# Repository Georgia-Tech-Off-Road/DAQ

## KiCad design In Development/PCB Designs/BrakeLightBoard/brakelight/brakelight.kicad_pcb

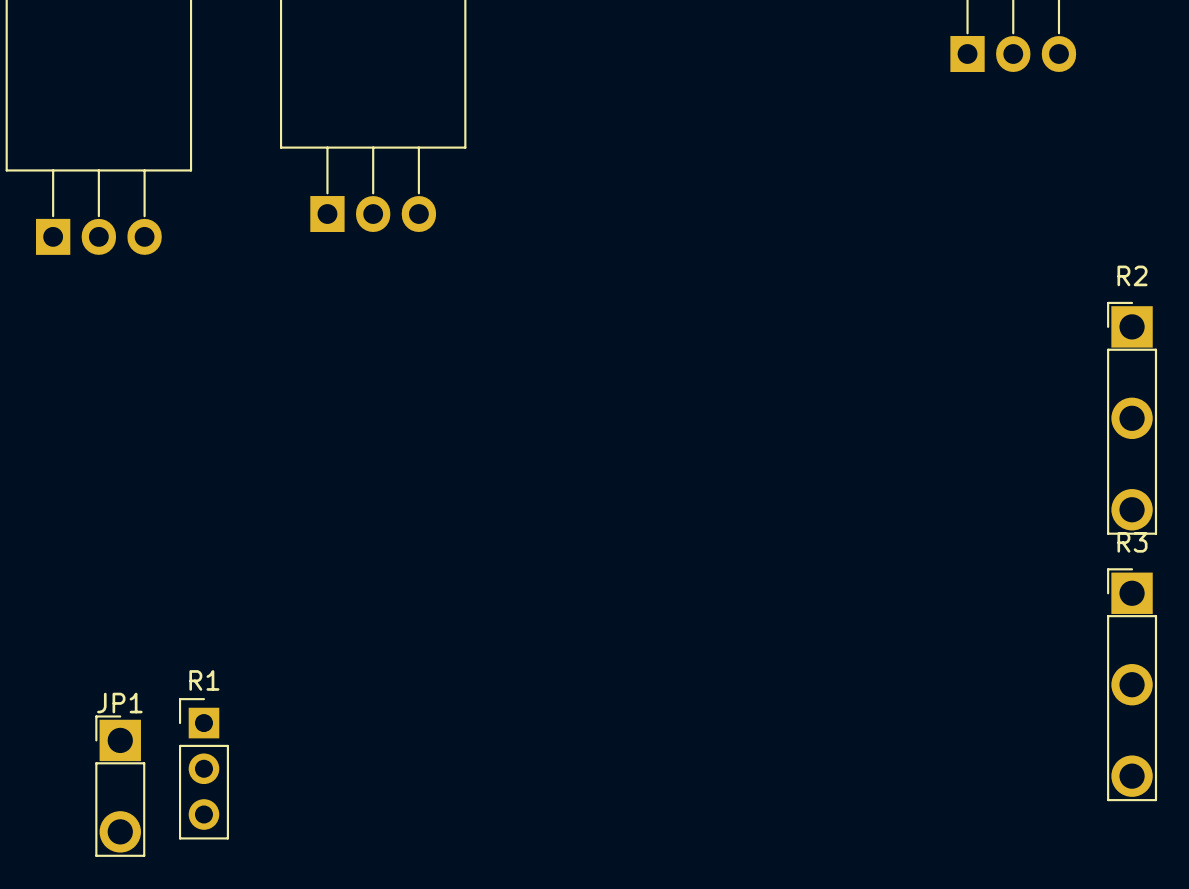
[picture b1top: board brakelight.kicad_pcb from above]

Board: 2 copper layers, 7 parts (0 on the bottom side), 3 nets, no tracks yet.

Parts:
IC3: 78XXL; TO-220-3_Horizontal_TabDown
JP1: PINHD-1X2; PinHeader_1x02_P5.08mm_Vertical
Q1, Q2: SUP75N06-08; TO-220-3_Horizontal_TabDown
R1: R-TRIMM74W; PinHeader_1x03_P2.54mm_Vertical
R2, R3: 100K; PinHeader_1x03_P5.08mm_Vertical

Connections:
GND: Q1.3, Q2.3, R1.3, R2.2, R3.2
unnamed: Q1.1, R2.1
unnamed: Q2.1, R3.1

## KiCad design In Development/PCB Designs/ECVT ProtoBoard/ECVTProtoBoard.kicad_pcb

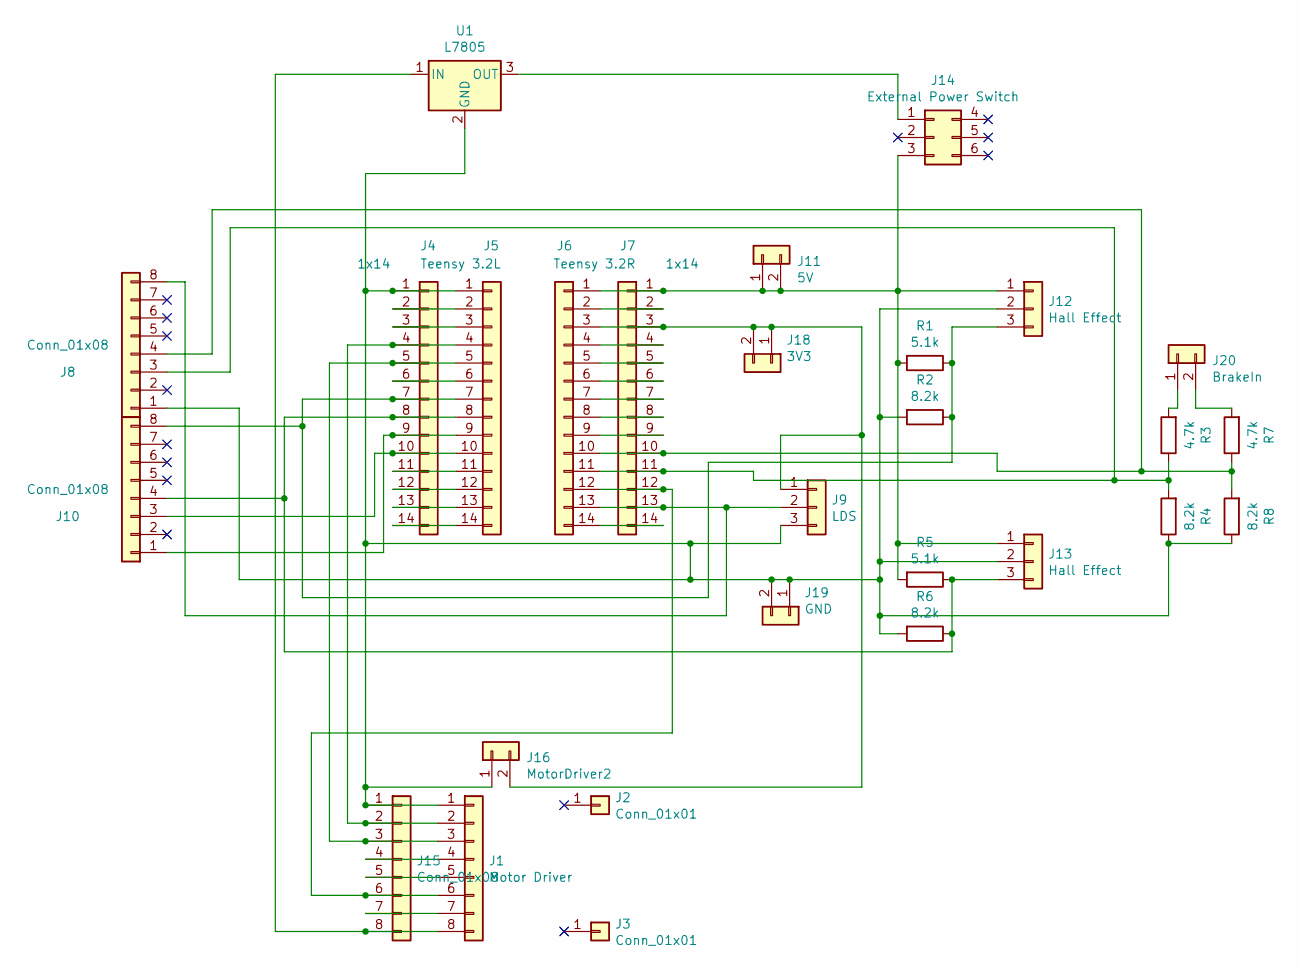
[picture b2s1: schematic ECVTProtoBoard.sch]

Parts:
J1: Motor Driver; PinHeader_1x08_P2.54mm_Vertical
J2, J3: Conn_01x01; PinHeader_1x01_P2.54mm_Vertical
J4, J7: 1x14; PinHeader_1x14_P2.54mm_Vertical
J5: Teensy 3.2L; PinHeader_1x14_P2.54mm_Vertical
J6: Teensy 3.2R; PinHeader_1x14_P2.54mm_Vertical
J8, J10: Conn_01x08; PinHeader_1x08_P2.00mm_Vertical
J9: LDS; PinHeader_1x03_P5.08mm_Vertical
J11: 5V; PinHeader_1x02_P2.54mm_Vertical
J12, J13: Hall Effect; PinHeader_1x03_P5.08mm_Vertical
J14: External Power Switch; PinHeader_2x03_P2.54mm_Vertical
J15: Conn_01x08; PinHeader_1x08_P2.54mm_Vertical
J16: MotorDriver2; PinHeader_1x02_P2.54mm_Vertical
J18: 3V3; PinHeader_1x02_P2.54mm_Vertical
J19: GND; PinHeader_1x02_P2.54mm_Vertical
J20: BrakeIn; PinHeader_1x02_P5.08mm_Vertical
R1, R5: 5.1k; R_Axial_DIN0207_L6.3mm_D2.5mm_P7.62mm_Horizontal
R2, R4, R6, R8: 8.2k; R_Axial_DIN0207_L6.3mm_D2.5mm_P7.62mm_Horizontal
R3, R7: 4.7k; R_Axial_DIN0207_L6.3mm_D2.5mm_P7.62mm_Horizontal
U1: L7805; TO-220-3_Horizontal_TabDown

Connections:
unnamed: J1.1, J4.1, J5.1, J8.1, J9.3, J12.2, J13.2, J15.1, J16.1, J19.1, J19.2, R2.2, R4.1, R6.2, R8.1, U1.2 (GND)
unnamed: J1.2, J4.4, J5.4, J15.2
unnamed: J1.3, J4.5, J5.5, J15.3
unnamed: J1.4, J15.4
unnamed: J1.5, J15.5
unnamed: J1.6, J6.12, J7.12, J15.6
unnamed: J1.7, J15.7
unnamed: J1.8, J15.8, U1.1 (IN)
unnamed: J4.2, J5.2
unnamed: J4.3, J5.3
unnamed: J4.6, J5.6
unnamed: J4.11, J5.11
unnamed: J4.12, J5.12
unnamed: J4.13, J5.13
unnamed: J4.14, J5.14
unnamed: J6.2, J7.2
unnamed: J6.4, J7.4
unnamed: J6.5, J7.5
unnamed: J6.6, J7.6
unnamed: J6.7, J7.7
unnamed: J6.8, J7.8
unnamed: J6.9, J7.9
unnamed: J6.10, J7.10, J8.4, R7.1, R8.2
unnamed: J6.11, J7.11, J8.3, R3.1, R4.2
unnamed: J6.13, J7.13, J8.8, J9.2
unnamed: J6.14, J7.14
unnamed: J4.9, J5.9, J10.1
unnamed: J4.10, J5.10, J10.3
unnamed: J4.8, J5.8, J10.4, J13.3, R5.1, R6.1
unnamed: J4.7, J5.7, J10.8, J12.3, R1.1, R2.1
unnamed: J6.1, J7.1, J11.1, J11.2, J12.1, J13.1, J14.3, R1.2, R5.2
unnamed: J14.1, U1.3 (OUT)
unnamed: J6.3, J7.3, J9.1, J16.2, J18.1, J18.2
unnamed: J20.1, R3.2
unnamed: J20.2, R7.2

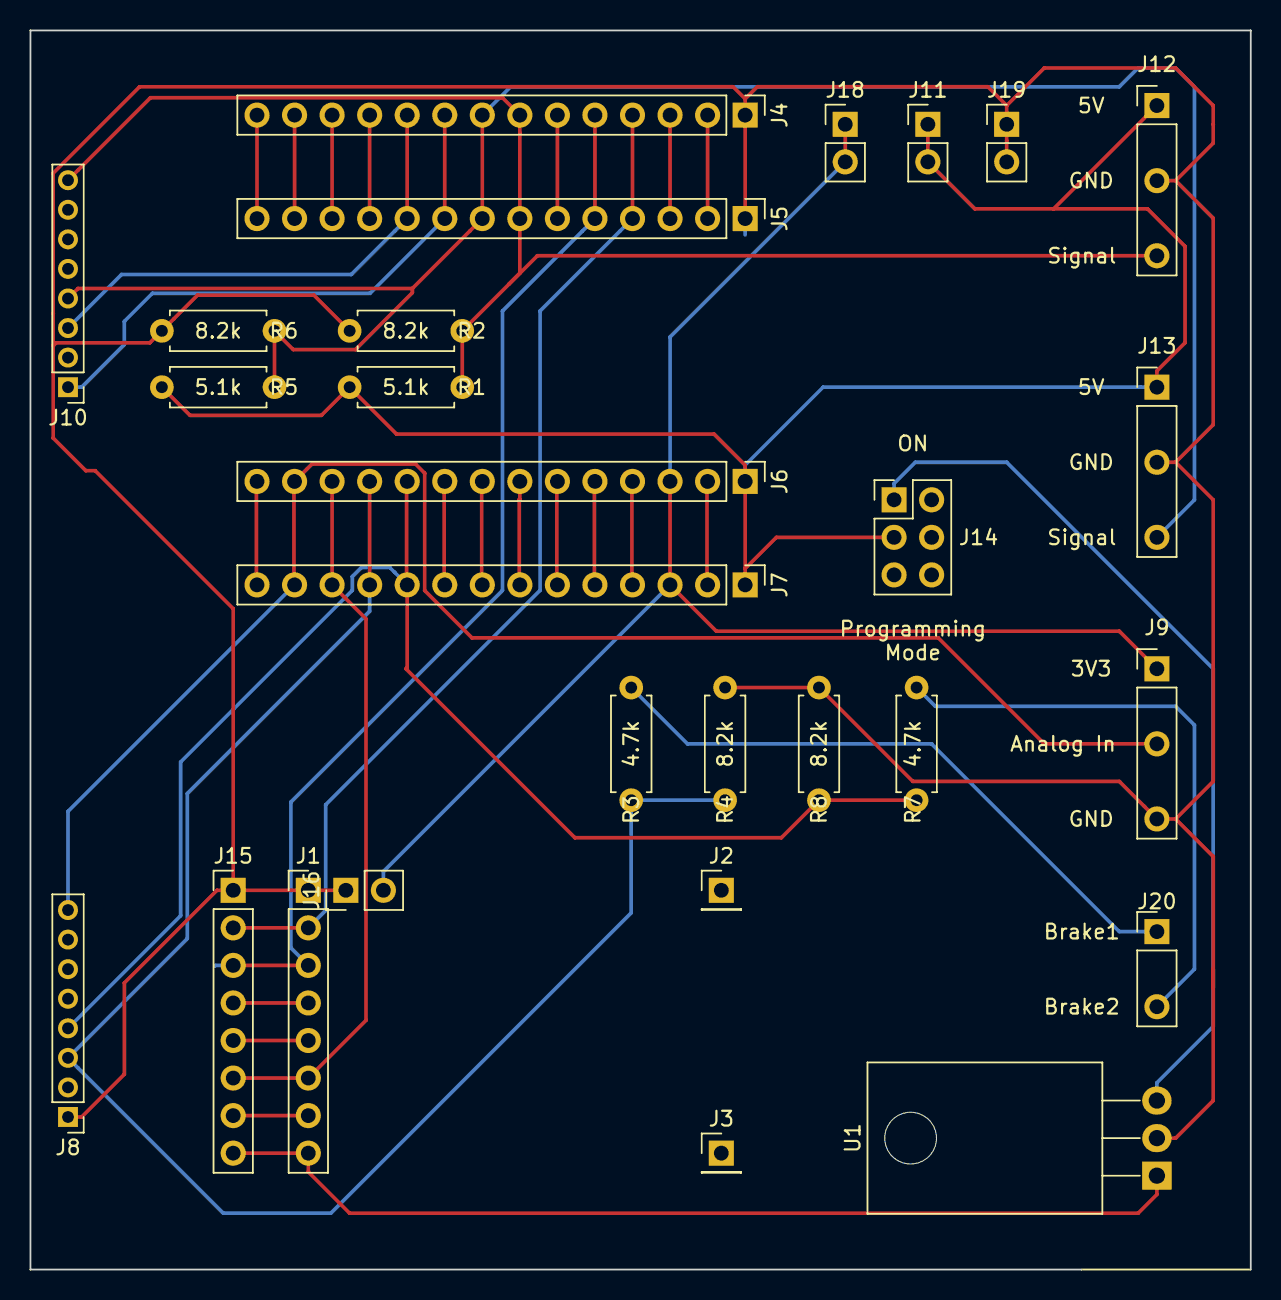
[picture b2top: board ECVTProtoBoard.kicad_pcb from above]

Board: 2 copper layers, 82.6 x 83.8 mm, 28 parts (0 on the bottom side), 35 nets.

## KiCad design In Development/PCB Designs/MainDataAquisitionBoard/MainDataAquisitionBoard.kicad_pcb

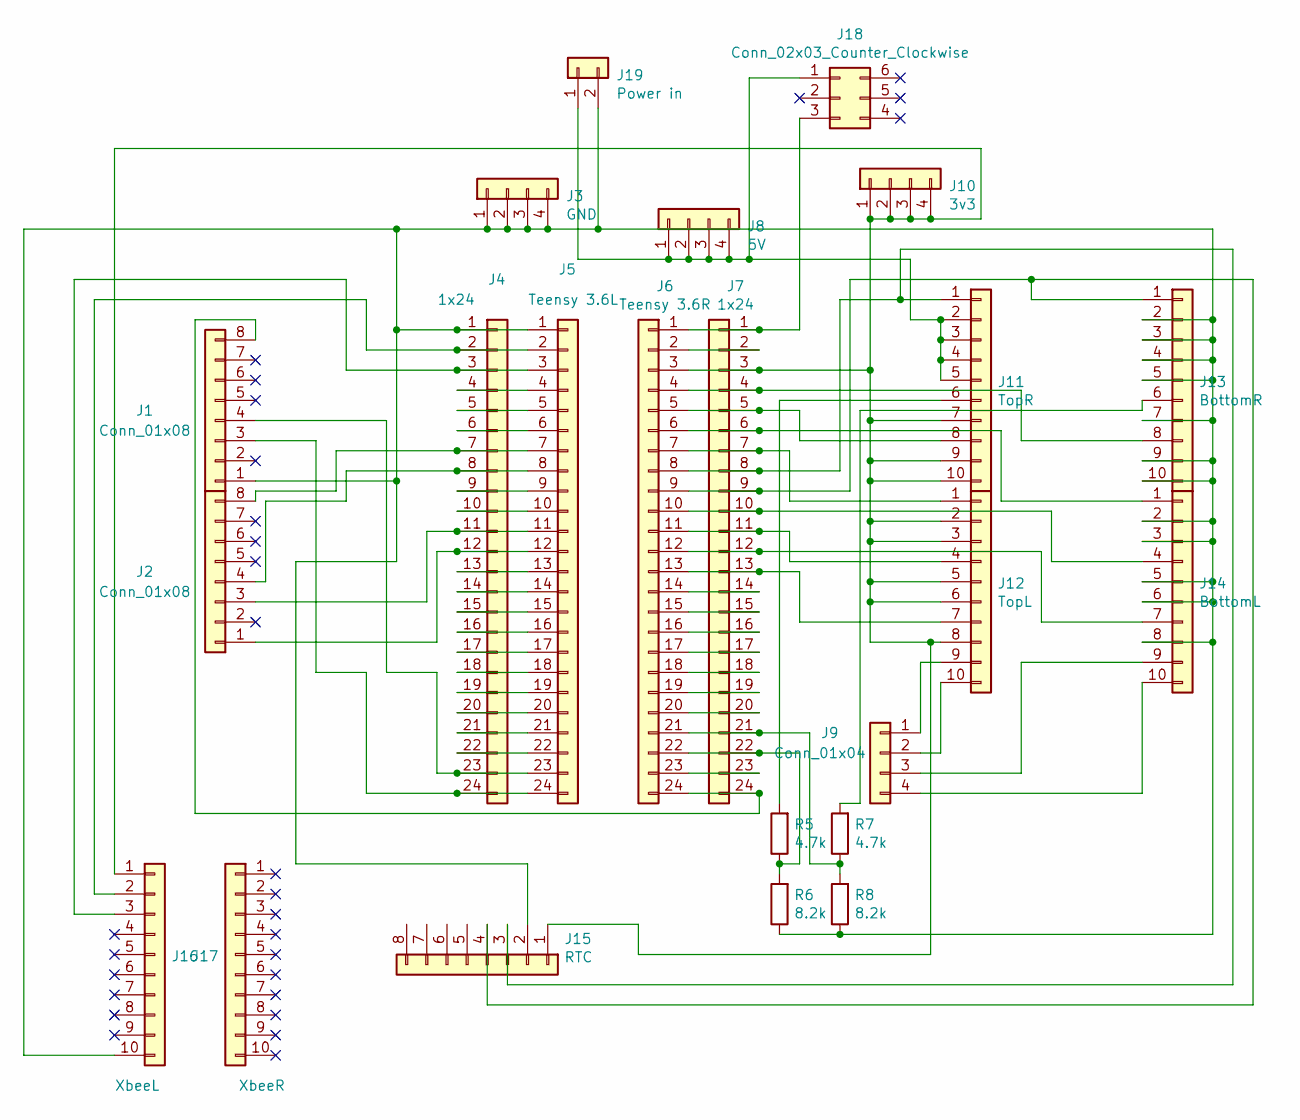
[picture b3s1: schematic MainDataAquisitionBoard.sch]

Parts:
J1, J2: Conn_01x08; PinHeader_1x08_P2.00mm_Vertical
J3: GND; PinHeader_1x04_P2.54mm_Vertical
J4, J7: 1x24; PinHeader_1x24_P2.54mm_Vertical
J5: Teensy 3.6L; PinHeader_1x24_P2.54mm_Vertical
J6: Teensy 3.6R; PinHeader_1x24_P2.54mm_Vertical
J8: 5V; PinHeader_1x04_P2.54mm_Vertical
J9: Conn_01x04; PinHeader_1x04_P2.54mm_Vertical
J10: 3v3; PinHeader_1x04_P2.54mm_Vertical
J11: TopR; PinHeader_1x10_P5.08mm_Vertical
J12: TopL; PinHeader_1x10_P5.08mm_Vertical
J13: BottomR; PinHeader_1x10_P5.08mm_Vertical
J14: BottomL; PinHeader_1x10_P5.08mm_Vertical
J15: RTC; PinHeader_1x08_P2.54mm_Vertical
J16: XbeeL; PinHeader_1x10_P2.54mm_Vertical
J17: XbeeR; PinHeader_1x10_P2.54mm_Vertical
J18: Conn_02x03_Counter_Clockwise; PinHeader_2x03_P2.54mm_Vertical
J19: Power in; PinHeader_1x02_P5.08mm_Vertical
R5, R7: 4.7k; R_Axial_DIN0207_L6.3mm_D2.5mm_P7.62mm_Horizontal
R6, R8: 8.2k; R_Axial_DIN0207_L6.3mm_D2.5mm_P7.62mm_Horizontal

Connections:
unnamed: J1.1, J3.1, J3.2, J3.3, J3.4, J4.1, J5.1, J13.2, J13.3, J13.4, J13.5, J13.7, J13.9, J13.10, J14.2, J14.3, J14.5, J14.6, J14.8, J15.2, J16.10, J19.2, R6.1, R8.1
unnamed: J1.3, J4.24, J5.24
unnamed: J1.4, J4.23, J5.23
unnamed: J1.8, J6.24, J7.24
unnamed: J2.1, J4.12, J5.12
unnamed: J2.3, J4.11, J5.11
unnamed: J2.4, J4.8, J5.8
unnamed: J2.8, J4.7, J5.7
unnamed: J4.4, J5.4
unnamed: J4.5, J5.5
unnamed: J4.6, J5.6
unnamed: J4.9, J5.9
unnamed: J4.10, J5.10
unnamed: J4.13, J5.13
unnamed: J4.14, J5.14
unnamed: J4.15, J5.15
unnamed: J4.16, J5.16
unnamed: J4.17, J5.17
unnamed: J4.18, J5.18
unnamed: J4.19, J5.19
unnamed: J4.20, J5.20
unnamed: J4.21, J5.21
unnamed: J4.22, J5.22
unnamed: J6.2, J7.2
unnamed: J6.14, J7.14
unnamed: J6.15, J7.15
unnamed: J6.16, J7.16
unnamed: J6.17, J7.17
unnamed: J6.18, J7.18
unnamed: J6.19, J7.19
unnamed: J6.20, J7.20
unnamed: J6.21, J7.21, R7.1, R8.2
unnamed: J6.22, J7.22, R5.1, R6.2
unnamed: J6.23, J7.23
unnamed: J6.3, J7.3, J10.1, J10.2, J10.3, J10.4, J11.7, J11.9, J11.10, J12.2, J12.3, J12.5, J12.6, J12.8, J15.1, J16.1
unnamed: J6.8, J7.8, J11.1, J15.3
unnamed: J8.1, J8.2, J8.3, J8.4, J11.2, J11.3, J11.4, J11.5, J18.1, J19.1
unnamed: J11.6, R5.2
unnamed: J6.5, J7.5, J11.8
unnamed: J6.7, J7.7, J12.1
unnamed: J6.11, J7.11, J12.4
unnamed: J6.13, J7.13, J12.7
unnamed: J9.1, J12.9
unnamed: J9.2, J12.10
unnamed: J6.9, J7.9, J13.1, J15.4
unnamed: J13.6, R7.2
unnamed: J6.4, J7.4, J13.8
unnamed: J6.6, J7.6, J14.1
unnamed: J6.10, J7.10, J14.4
unnamed: J6.12, J7.12, J14.7
unnamed: J9.3, J14.9
unnamed: J9.4, J14.10
unnamed: J4.2, J5.2, J16.2
unnamed: J4.3, J5.3, J16.3
unnamed: J6.1, J7.1, J18.3

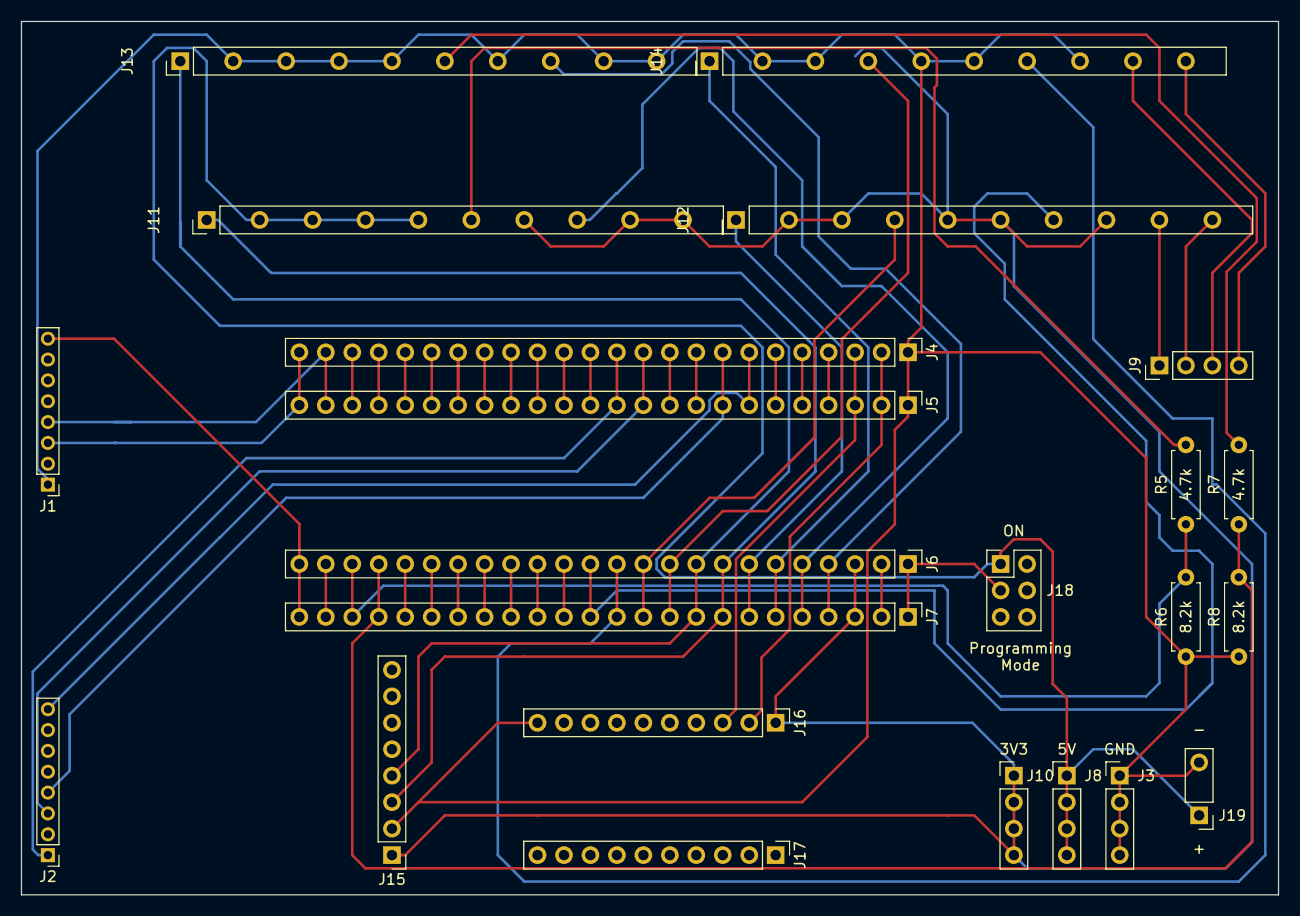
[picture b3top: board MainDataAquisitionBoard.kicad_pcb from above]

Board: 2 copper layers, 120.7 x 83.8 mm, 23 parts (0 on the bottom side), 55 nets.

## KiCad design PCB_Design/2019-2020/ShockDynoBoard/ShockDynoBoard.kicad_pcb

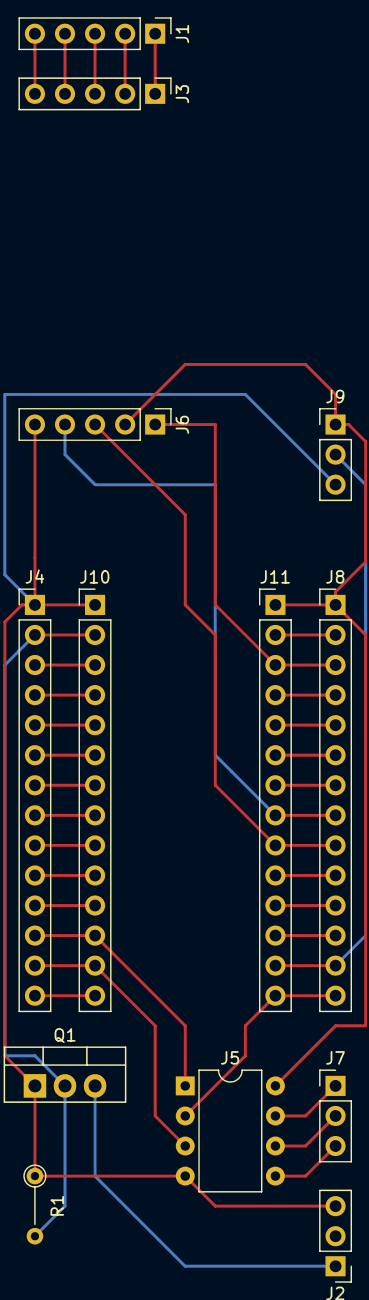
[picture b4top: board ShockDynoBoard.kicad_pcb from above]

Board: 2 copper layers, 13 parts (0 on the bottom side), 37 nets.

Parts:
J1: Load Cell; PinHeader_1x05_P2.54mm_Vertical
J2: ESC Switch; PinHeader_1x03_P2.54mm_Vertical
J3: HX711 L; PinHeader_1x05_P2.54mm_Vertical
J4, J8: 1x14; PinHeader_1x14_P2.54mm_Vertical
J5: MSP4131; DIP-8_W7.62mm
J6: HX711 R; PinHeader_1x05_P2.54mm_Vertical
J7: ESC; PinHeader_1x03_P2.54mm_Vertical
J9: LDS; PinHeader_1x03_P2.54mm_Vertical
J10: Teensy 3.2 L; PinHeader_1x14_P2.54mm_Vertical
J11: Teensy 3.2 R; PinHeader_1x14_P2.54mm_Vertical
Q1: MOSFET; TO-220-3_Vertical
R1: 20k; R_Axial_DIN0204_L3.6mm_D1.6mm_P5.08mm_Vertical

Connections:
unnamed: J1.1, J3.1
unnamed: J1.2, J3.2
unnamed: J1.3, J3.3
unnamed: J1.4, J3.4
unnamed: J1.5, J3.5
unnamed: J2.1, Q1.3
unnamed: J5.5, J7.3
unnamed: J5.6, J7.2
unnamed: J5.7, J7.1
unnamed: J2.3, J4.1, J5.4, J6.5, J9.3, J10.1, Q1.1, R1.1
unnamed: J4.2, J10.2, Q1.2, R1.2
unnamed: J4.3, J10.3
unnamed: J4.4, J10.4
unnamed: J4.5, J10.5
unnamed: J4.6, J10.6
unnamed: J4.7, J10.7
unnamed: J4.8, J10.8
unnamed: J4.9, J10.9
unnamed: J4.10, J10.10
unnamed: J4.11, J10.11
unnamed: J4.12, J5.1, J10.12
unnamed: J4.13, J5.3, J10.13
unnamed: J4.14, J10.14
unnamed: J5.8, J6.2, J8.1, J9.1, J11.1
unnamed: J8.2, J11.2
unnamed: J6.1, J8.3, J11.3
unnamed: J8.4, J11.4
unnamed: J8.5, J11.5
unnamed: J8.6, J11.6
unnamed: J8.7, J11.7
unnamed: J6.4, J8.8, J11.8
unnamed: J6.3, J8.9, J11.9
unnamed: J8.10, J11.10
unnamed: J8.11, J11.11
unnamed: J8.12, J11.12
unnamed: J8.13, J9.2, J11.13
unnamed: J5.2, J8.14, J11.14

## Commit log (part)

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2020-12-27 Testing if I can push to remote
2020-12-31 IMU330DHCX Final Code
2020-12-31 IMU330DHCX Header Upload
2021-01-03 Added the HE sensor case for Rev2
2021-01-14 Add ISM330DHCX Library
2021-01-15 Conceptual Brainstorming Changes
2021-01-15 Added diff library for eagle
2021-01-15 Added relevant mailing lists for recruitment emails.
2021-01-15 Updated .gitignore and cleaned up Eagle autosaves
2021-01-15 Removed Eagle Libraries
2021-01-16 Created HESensorRev3 case and added documentation
2021-01-16 Added STL Files for Printing
2021-01-16 Created file for IMU
2021-01-16 Increase ranges for accel, gyro, and data rates
2021-01-16 Documentation changes
2021-01-17 Eagle files for PCB
2021-01-18 Added schematic and board files
2021-01-20 Updated Eagle board and software
    Added female headers, routed HE inputs
    Added theoretical diff controller code basis
2021-01-23 Made minor edits to documentation
2021-01-23 Added step in eagle libraries guide
2021-01-27 Test example
2021-01-31 Added small functions to utility
2021-01-31 Changed Lib .readme
2021-01-31 Added automatic Arduino library symlinks generator
2021-02-01 Resized speed sensor case for larger shaft
2021-02-03 Fixed parts so that they can actually be assembled.
2021-02-05 Added STL Files for IMU Case Printing
2021-02-09 Renamed folder from "new_project" to "Dyno Board"
2021-02-10 Renamed folder and added Load Cell Manual.
2021-02-13 Fixed data being deleted after stopped collecting bug
2021-02-13 Added changes that I do not remember
2021-02-18 Created documentation for the engine dyno
2021-02-19 Added documentation for engine dyno
2021-02-19 Added lots of changes for first working prototype
2021-02-24 replaced old motor driver; added local libraries
2021-02-24 Minor bug fixes
2021-02-28 pcb from 02-28
2021-03-04 edited h-bridge
2021-03-04 Minor changes on PCB, ready for manufacturing
2021-03-07 Began work on UARTComms class and Sensor class
2021-03-07 small changes to Sensor
2021-03-07 added changes to update function
2021-03-07 Adding __init__ for EngineDyno Layout
2021-03-10 Pseudocoded rest of Comms functions to be written
2021-03-12 Reconstructed FreqMeasureMulti without using FreqMeasureMulti library
2021-03-12 Moved IMU Lib folder code to Libraries folder
2021-03-12 Moved Dyno code in Lib folder to Libraries folder
2021-03-16 Added functionality for zero rpm
2021-03-17 Finished Aux Daq Case
2021-03-19 Seven Segment Code done
2021-03-20 added matlab file for theoretical speed sensor calculations
2021-03-21 Added update for serial input
2021-03-21 Auto stash before merge of "differential_controller" and "origin/differential_controller"
2021-03-21 Fixed compilation errors and implemented switch/serial control mode
2021-03-24 Finished theoretical implementation using FreqMeasureMulti
2021-03-25 Adding data parser for recording and graphing data collected from sensors
2021-03-26 Adding the data parser to change bin data files in to usable data to graph and add to an excel sheet
2021-03-26 Reversed motor pins to work with new differential
2021-03-26 Working UARTComms and SDWrite libraries. Next step is extending Sensor functionality.
2021-03-26 temporary commit
2021-03-26 Tidying the parser and preparing for plotting
2021-03-26 Sensor updates, LDS example
2021-03-27 Fixed some problems with LDS example, Sensor id bug still exists---id needs to be 1 byte for now
2021-03-27 aux daq unit code with two sensors
2021-03-27 Quick fix for diff controller breaking when moving to state 1 and state2
2021-03-27 Added more sensor libraries
2021-03-27 Give to Akash code
2021-03-28 Changes from grind day
2021-03-30 Beginning data parser optimizations
2021-04-01 Need to change branches
2021-04-01 Small changes to DataCollection
2021-04-02 Adding more cleanup to parser
2021-04-02 Added functions to implement for data import
2021-04-02 Added Sensor ID's to Daata
2021-04-04 Before merge with aux_daq_util
2021-04-04 Adding most Import functionality and updating Data and SensorId accordingly
2021-04-04 Added Pinout image and modified Dyno_test to follow pinout
2021-04-06 Renamed Folder to Engine_Dyno
2021-04-06 Updated HEtest.ino to work with new HE Sensor library
2021-04-06 Added psedu-code/code for speed sensor?
    Please double-check
2021-04-07 Finished minimum worked version of SpeedSensor
2021-04-07 Added SpeedSensor to Sensor.h
2021-04-07 Cleaning up parser, adding csv file for data, and beginning update to Sensor objects and ID's
2021-04-07 Updating Sensor ID numbers
2021-04-07 hotfix
2021-04-07 Code ready for dyno test
2021-04-09 Added SerialTest.ino
2021-04-09 Git witchcraft merge
2021-04-10 Comments added
2021-04-11 Code uploaded for the 4/11/2021 test day
    Syntax errors fixed
2021-04-13 Code uploaded for test day 4/11/21
2021-04-17 Fixed errors with Sensor Class
2021-04-17 Adding data parsers
2021-04-17 Updated SensorId
2021-04-17 Changes to mock wireless testing
2021-04-17 Manual merge of dashboard into master
2021-04-21 Adding syntax fixes in import
2021-04-21 Changing serial port to None to get it working
2021-04-23 On the verge of glory
2021-04-25 pls no conflict
2021-04-28 Made better averaging algorithm for speed sensor
2021-05-01 Updated Dashboard Code (non-working)
2021-05-01 Display diff position on dashboard
2021-05-01 Added StateSensor and diff_state functionality for writing diff_state to h_seg on dash
2021-05-12 Updated documentation template
2021-06-02 DashHub code changes from Arizona
2021-06-18 Removed Documentation
2021-06-18 Removed Resources Folder
2021-06-26 Removed HallEffectSpeedSensor
2021-06-29 Removed Libraries
2021-07-08 Updates to First Dyno test
2021-08-21 Added ability to zero load cell
2021-09-03 Created new branch and folder for new 2022 aux_daq
2021-09-06 Added rough draft of shockdyno arduino code
2021-09-12 Added optional headers for strain gauge breakout
2021-09-12 added project for shock dyno
2021-09-19 Working on board files
2021-09-19 Minor DRC fixes and trace thickening
2021-09-19 Minor silkscreen changes
2021-09-19 completed shock dyno PCB schematic
2021-09-20 Boards designs before 9/19 design review
2021-09-22 Moved phat connector
2021-09-24 shock dyno PCB updates
2021-09-26 Just a bit of work I did on Tuesday
2021-09-26 Added kill motor scenario and fixed scale for motor_control
2021-09-26 added name to shock dyno PCB
2021-09-27 More work done to dash hub and dial, gps board added
2021-09-27 Adding design draft of comms testing board
2021-09-28 Finished everything except silkscreen
2021-09-29 final touches to shock dyno PCB
2021-09-29 Adding finished comms testing board
2021-09-29 Updated silkscreen
2021-09-29 final touches to shock dyno PCB part 3
2021-10-01 Linear Regulator
2021-10-06 Added wireless receiver PCB
2021-10-08 Added new linear regulator and XBee silkscreen to dashhub
2021-10-10 Added gps to dashhub
2021-10-15 Added OLED
2021-10-17 Added missing capacitor values
2021-10-17 Moving stuff around on the dashhub #pain
2021-10-19 Changed names on dashboard to reflect pins
2021-10-20 Changed regulator placement
2021-10-22 Fixed the dashhub #everything
2021-10-27 Added resistor values to dashhub and board
2021-10-31 Fixed IMU test code
2021-11-04 IMU Code works with aux_daq
2021-11-05 OLED code added
2021-11-05 Added OLED code
2021-11-05 Added Aux Daq Code and wireless comms throughput
2021-11-12 Test day AuxDaq code
2021-12-07 Added Testing Day Nov 20 Code
    It doesn't work
2021-12-07 Finished routing aux daq
2021-12-13 Started making Aux Daq V2 Case
2021-12-29 Did Aux Daq Design Review
2022-01-14 oriented load cell connector correctly
2022-01-14 added labels to silkscreen on shock dyno PCB
2022-01-14 Edited Dashboard code
2022-01-19 Updated Aux Daq PCB to include LED and button outputs
2022-01-21 Added aux daq definitions file
2022-01-24 Finished shock dyno updates
2022-02-02 Removed incorrect IMU case
2022-02-06 Updated all dashboard stuff
2022-02-11 Dashboard Code Organization
2022-02-13 modified Shock_Dyno.ino for ads8688
2022-02-20 fixed Shock Dyno disable
2022-02-28 removed relay from shock dyno
2022-03-02 Removed bad dashboard code
2022-03-04 changed strain gauge board connectors to microfit
2022-03-04 Added new Light Gate boards
2022-03-06 Light Gate Updates
2022-03-06 Fixeed light gate start board
2022-03-07 Created second aux daq digital breakout
2022-03-09 Coded light gates
2022-03-13 Attached GPS block for dashboard
2022-04-01 Updated Wireless Receiver Code
2022-04-03 Updated DynoTest Code
2022-04-07 COde from testing day
2022-04-10 Updated aux daq case design and added demo code for end of year review
2022-04-24 added power trace to shock dyno board ADC
2022-04-24 added more clearance for standoff pins on shock dyno
2022-04-24 edit dashboard code
2022-05-06 Wrote CVTStiffness testing code
2022-05-06 FIXED DASHBOARD LETS GOOO
2022-06-02 Dashboard code from Tennessee
2022-08-25 Engine dyno speed sensor updates
2022-09-13 new pcb files
2022-09-28 Updated to 7mil trace instead of 5mil
2022-10-02 Working on dashboard code
2022-10-09 CODE
2022-10-30 Updated pull ups on dashboard
2022-11-03 Wireless Communications Consolidation
2022-11-18 change file name
2022-11-30 Battery box and commsboardv2 update
2022-12-02 Updated for better dimensions
2023-01-13 Updated dashboard speed formulas and added some documentation comments
2023-01-15 GPS test code started
2023-01-16 Updated dashboard mps names for c++ conflict
2023-01-20 Created PCB For Driver Comms Board + Misc.
    Edited sketch for driver comms test board and then designed corresponding PCB. Pushed some changes with schock dyno and imu test code that are minor (and I don't remember making).
2023-01-20 Updated dash hub to power GPS with 5V
2023-01-25 Battery Box Update v4
    Changed sides of radio antenna hole and wires hole.
2023-01-27 Finalized PCB and started code
2023-02-01 Fully Updated Code to send to Driver
2023-02-03 Created code for receiving messages on dashboard board
2023-02-05 Finalized dashboard code to receive and display messages to driver
2023-02-17 Changes so only sends when a different message is sent
2023-02-26 Testing ADC's on auxdaq, made test ino file and copied board files from last year to edit them
2023-03-03 Updating Code for Testing Driver Comms
2023-03-03 Tested and Finalized Receiver Code
2023-03-08 Comms Test Board update
    changed some stuff
2023-03-08 CVT Temp Sensor PCB
    Version 1.0
2023-03-08 Added connector to IMU board
2023-03-10 Finished IMU board
2023-03-10 not sure what this is
2023-04-16 Updated Sender Board
    Corrected orientation of Xbee and also power supply.
2023-04-17 Updated dashboard code to use onboard indication LEDS
    This is different from driver comms board indication
2023-04-21 Updated Driver Message Board so that LEDs work
2023-04-29 auxDaq code used for testing days in April
2023-04-29 code that maybe interfaces sdWrite button from daata to auxDaq
2023-05-04 Updated dashboard with gps
2023-05-05 Teensy to teensy comms maybe
2023-05-06 Fix block ids
2023-05-06 Bug fix
2023-05-07 print gps
2023-08-25 same as below commit
2023-08-30 imudash wip
2023-09-01 Add dashboard IMU to comms path
2023-09-09 Switch speed sensors
2023-09-17 Unneeded
2023-09-24 Fix force sensor maybe
2023-10-01 test
    random test push to fix vishnav's git set up
2023-10-01 Revert "test"
    This reverts commit ca83d801667cfc2b1897a25c9061b99a7f00245b.
2024-04-04 changed pin assignments and commented out dashboard signals
2024-04-14 LEDS
2024-04-16 changed port numbers, fixed constructor
2024-04-21 Changes On Ohio 2023 to add LEDs
